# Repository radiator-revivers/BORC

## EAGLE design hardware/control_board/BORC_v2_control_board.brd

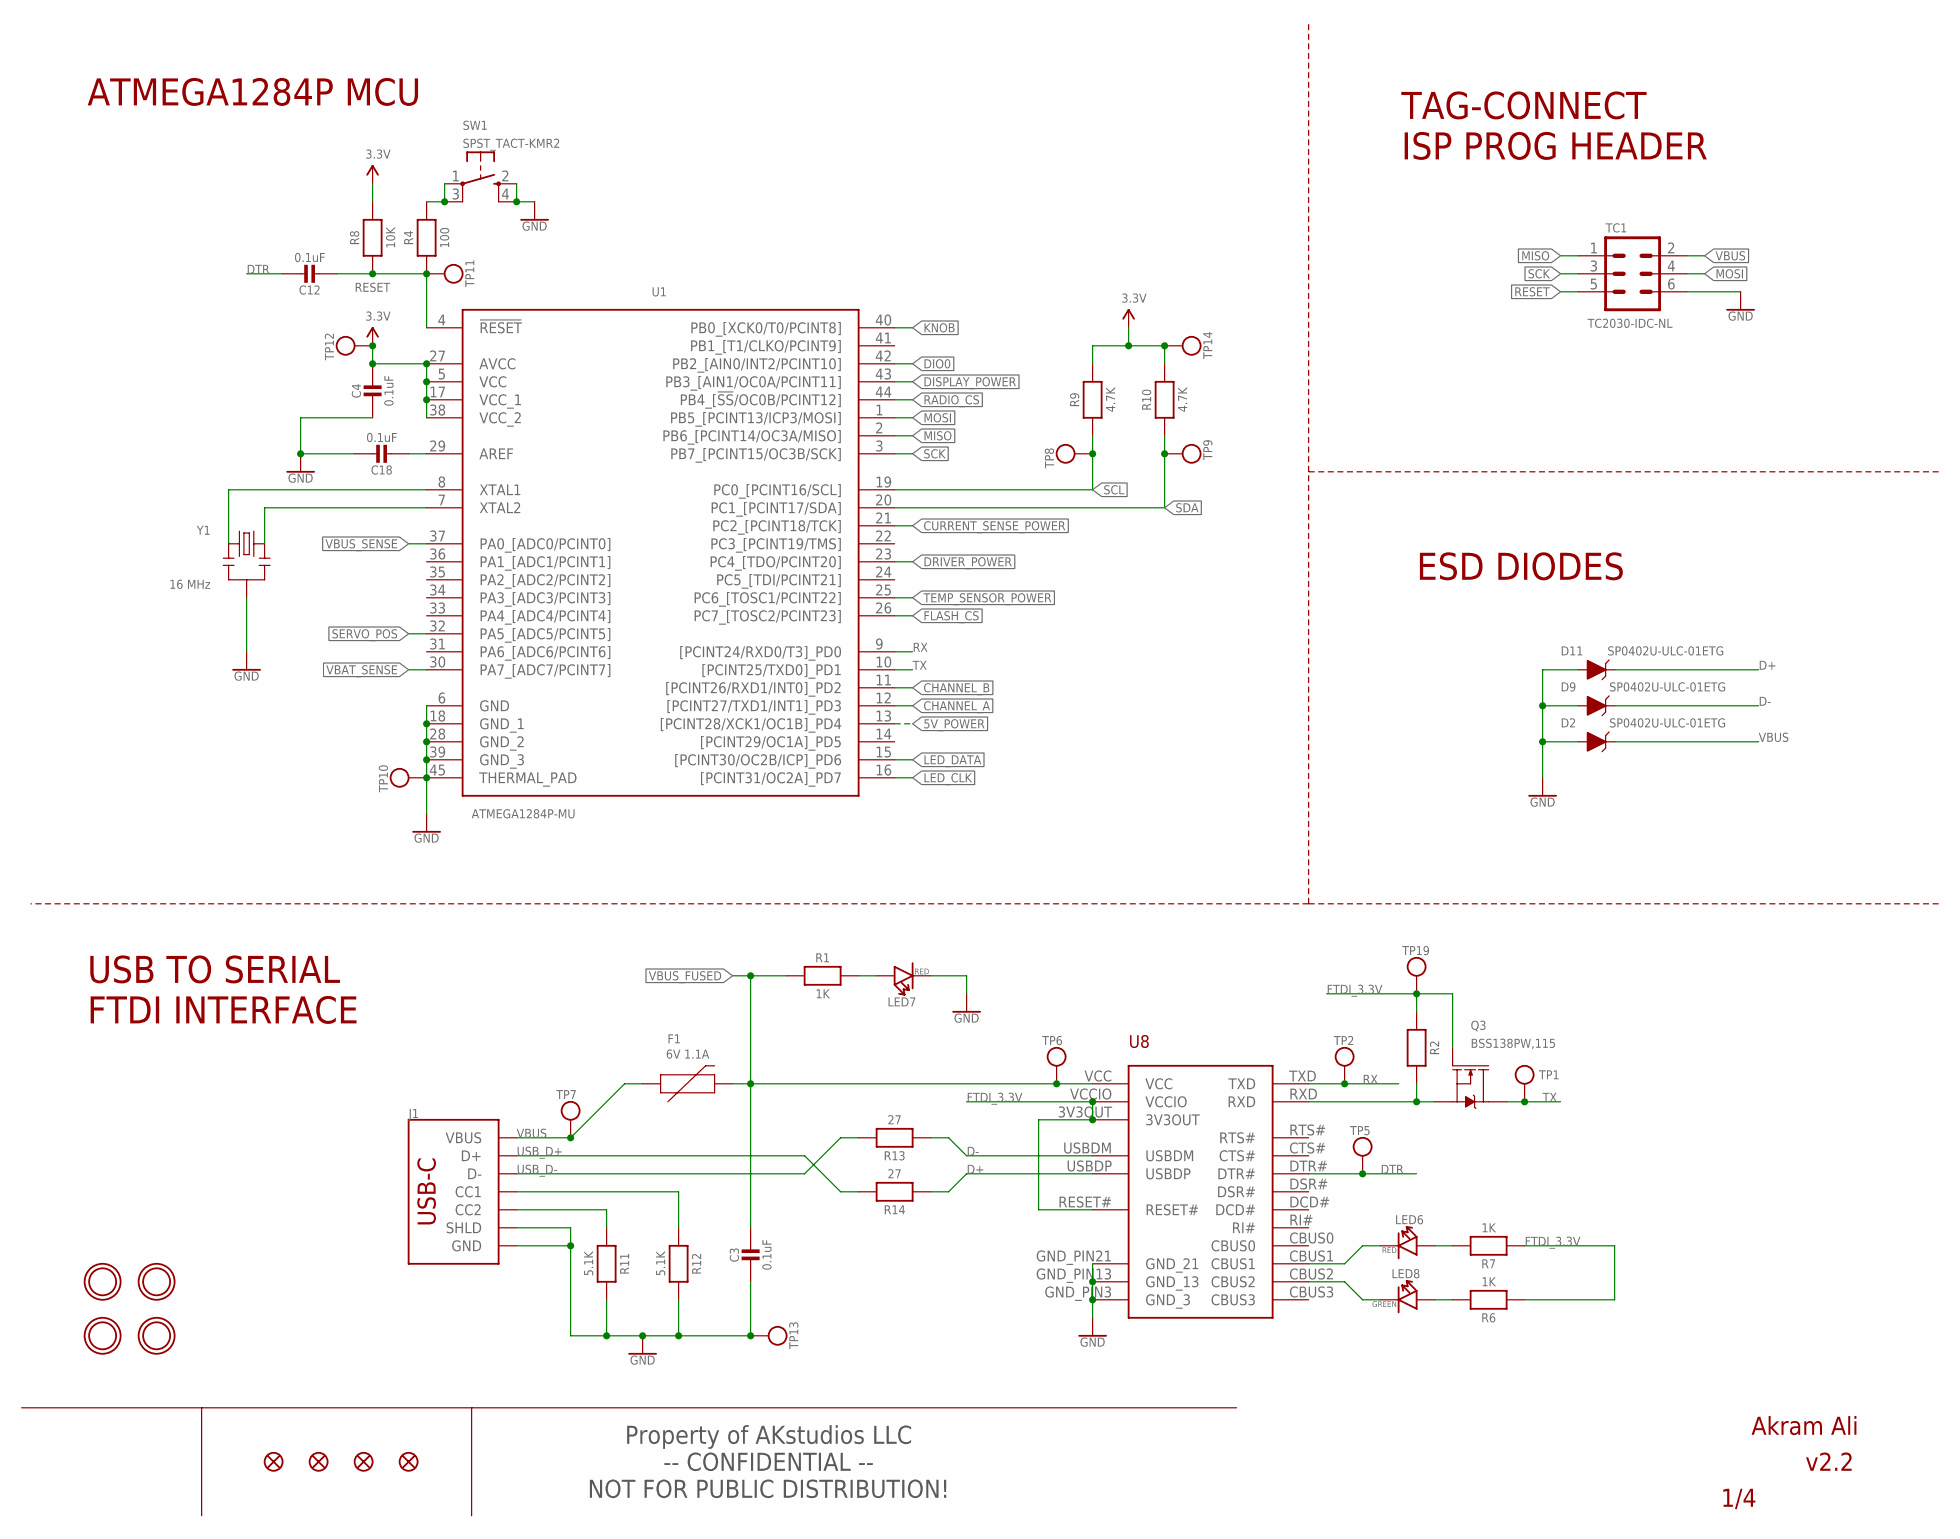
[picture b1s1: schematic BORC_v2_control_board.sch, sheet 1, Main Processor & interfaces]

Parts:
C3, C4, C12, C18: 0.1uF; MICROBUILDER__0402MP; MPN GRM155R71H104KE14D
D2, D9, D11: SP0402U-ULC-01ETG; 0402; MPN SP0402U-ULC-01ETG
F1: 6V 1.1A; 0805; MPN MF-PSML110/6-2
FID1, FID2, FID3, FID4: FIDUCIAL""; FIDUCIAL_1MM
J1: USB Female Type C Connector; USB-C-16P-2LAYER-PADS; MPN USB4105-GF-A
LED6, LED7: RED; LED-0402; MPN IN-S42ATR
LED8: GREEN; LED-0402; MPN IN-S42ATG
Q3: BSS138PW,115; SOT323; MPN BSS138PW,115
R1, R6, R7: 1K; MICROBUILDER__0402MP; MPN RC0402FR-071KL
R2, R8: 10K; MICROBUILDER__0402MP; MPN RC0402FR-7W10KL
R4: 100; MICROBUILDER__0402MP; MPN RC0402FR-07100RL
R9, R10: 4.7K; MICROBUILDER__0402MP; MPN RC0402FR-074K7L
R11, R12: 5.1K; MICROBUILDER__0402MP; MPN RC0402FR-135K1L
R13, R14: 27; MICROBUILDER__0402MP; MPN RC0402FR-0727RL
SW1: SPST_TACT-KMR2; KMR2; MPN KMR221GLFS
TC1: TC2030-IDC-NL
TP1: TX; MICROBUILDER_TESTPOINT_ROUND_1MM
TP2, TP5, TP6, TP7, TP8, TP9, TP10, TP11, TP12, TP13, TP14, TP19: RX; MICROBUILDER_TESTPOINT_ROUND_1MM
U1: ATMEGA1284P-MU; QFN50P700X700X100-45N; MPN ATMEGA1284P-MU
U8: FT231XQ-R; FTDI_FT231XQ-R_PACKAGE
U$8, U$9, U$10, U$11: MICROBUILDER_MOUNTINGHOLE2.5_THICK; MICROBUILDER_MOUNTINGHOLE_2.5_PLATED_THICK
Y1: 16 MHz; RESONATOR-SMD; MPN CSTNE16M0V530000R0

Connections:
5V_POWER: U1.13 ([PCINT28/XCK1/OC1B]_PD4); also elsewhere on the board
CHANNEL_A: U1.12 ([PCINT27/TXD1/INT1]_PD3); also elsewhere on the board
CHANNEL_B: U1.11 ([PCINT26/RXD1/INT0]_PD2); also elsewhere on the board
CURRENT_SENSE_POWER: U1.21 (PC2_[PCINT18/TCK]); also elsewhere on the board
D+: D11.C, R14.1, U8.USBDP
D-: D9.C, R13.1, U8.USBDM
DIO0: U1.42 (PB2_[AIN0/INT2/PCINT10]); also elsewhere on the board
DISPLAY_POWER: U1.43 (PB3_[AIN1/OC0A/PCINT11]); also elsewhere on the board
DRIVER_POWER: U1.23 (PC4_[TDO/PCINT20]); also elsewhere on the board
DTR: C12.1, TP5.P$1, U8.DTR#
FLASH_CS: U1.26 (PC7_[TOSC2/PCINT23]); also elsewhere on the board
FTDI_3.3V: Q3.1 (G), R2.1, R6.1, R7.1, TP19.P$1, U8.3V3OUT, U8.RESET#, U8.VCCIO
GND: C3.2, C4.2, C18.1, D2.A, D9.A, D11.A, J1.GND, J1.GND2 (GND), J1.SHLD1 (SHLD), J1.SHLD2 (SHLD), J1.SHLD3 (SHLD), J1.SHLD4 (SHLD), LED7.-, R11.2, R12.2, SW1.2 (S), SW1.4 (S1), TC1.6, TP10.P$1, TP13.P$1, U1.6 (GND), U1.18 (GND_1), U1.28 (GND_2), U1.39 (GND_3), U1.45 (THERMAL_PAD), U8.GND_PIN3 (GND_3), U8.GND_PIN13 (GND_13), U8.GND_PIN21 (GND_21), Y1.2; also elsewhere on the board
KNOB: U1.40 (PB0_[XCK0/T0/PCINT8]); also elsewhere on the board
LED_CLK: U1.16 ([PCINT31/OC2A]_PD7); also elsewhere on the board
LED_DATA: U1.15 ([PCINT30/OC2B/ICP]_PD6); also elsewhere on the board
MISO: TC1.1, U1.2 (PB6_[PCINT14/OC3A/MISO]); also elsewhere on the board
MOSI: TC1.4, U1.1 (PB5_[PCINT13/ICP3/MOSI]); also elsewhere on the board
unnamed: U1.8 (XTAL1), Y1.1
unnamed: LED7.+, R1.2
unnamed: U1.7 (XTAL2), Y1.3
unnamed: J1.B5 (CC2), R11.1
unnamed: J1.A5 (CC1), R12.1
unnamed: LED8.+, R6.2
unnamed: LED6.-, U8.CBUS1
unnamed: C18.2, U1.29 (AREF)
unnamed: LED8.-, U8.CBUS2
unnamed: R4.2, SW1.1, SW1.3 (P1)
unnamed: Q3.2 (S), R2.2, U8.RXD
unnamed: LED6.+, R7.2
RADIO_CS: U1.44 (PB4_[!SS!/OC0B/PCINT12]); also elsewhere on the board
RESET: C12.2, R4.1, R8.1, TC1.5, TP11.P$1, U1.4 (!RESET)
RX: TP2.P$1, U1.9 ([PCINT24/RXD0/T3]_PD0), U8.TXD
SCK: TC1.3, U1.3 (PB7_[PCINT15/OC3B/SCK]); also elsewhere on the board
SCL: R9.1, TP8.P$1, U1.19 (PC0_[PCINT16/SCL]); also elsewhere on the board
SDA: R10.1, TP9.P$1, U1.20 (PC1_[PCINT17/SDA]); also elsewhere on the board
SERVO_POS: U1.32 (PA5_[ADC5/PCINT5]); also elsewhere on the board
TEMP_SENSOR_POWER: U1.25 (PC6_[TOSC1/PCINT22]); also elsewhere on the board
TX: Q3.3 (D), TP1.P$1, U1.10 ([PCINT25/TXD0]_PD1)
USB_D+: J1.A6 (D+), J1.B6 (D+), R14.2
USB_D-: J1.A7 (D-), J1.B7 (D-), R13.2
VBAT_SENSE: U1.30 (PA7_[ADC7/PCINT7]); also elsewhere on the board
VBUS: D2.C, F1.1, J1.VBUS1 (VBUS), J1.VBUS2 (VBUS), TC1.2, TP7.P$1; also elsewhere on the board
VBUS_FUSED: C3.1, F1.2, R1.1, TP6.P$1, U8.VCC; also elsewhere on the board
VBUS_SENSE: U1.37 (PA0_[ADC0/PCINT0]); also elsewhere on the board
VCC: C4.1, R8.2, R9.2, R10.2, TP12.P$1, TP14.P$1, U1.5 (VCC), U1.17 (VCC_1), U1.27 (AVCC), U1.38 (VCC_2); also elsewhere on the board

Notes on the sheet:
-- CONFIDENTIAL -- NOT FOR PUBLIC DISTRIBUTION!
Property of AKstudios LLC
v2.2
Akram Ali
ATMEGA1284P MCU
TAG-CONNECT ISP PROG HEADER
USB TO SERIAL FTDI INTERFACE
ESD DIODES

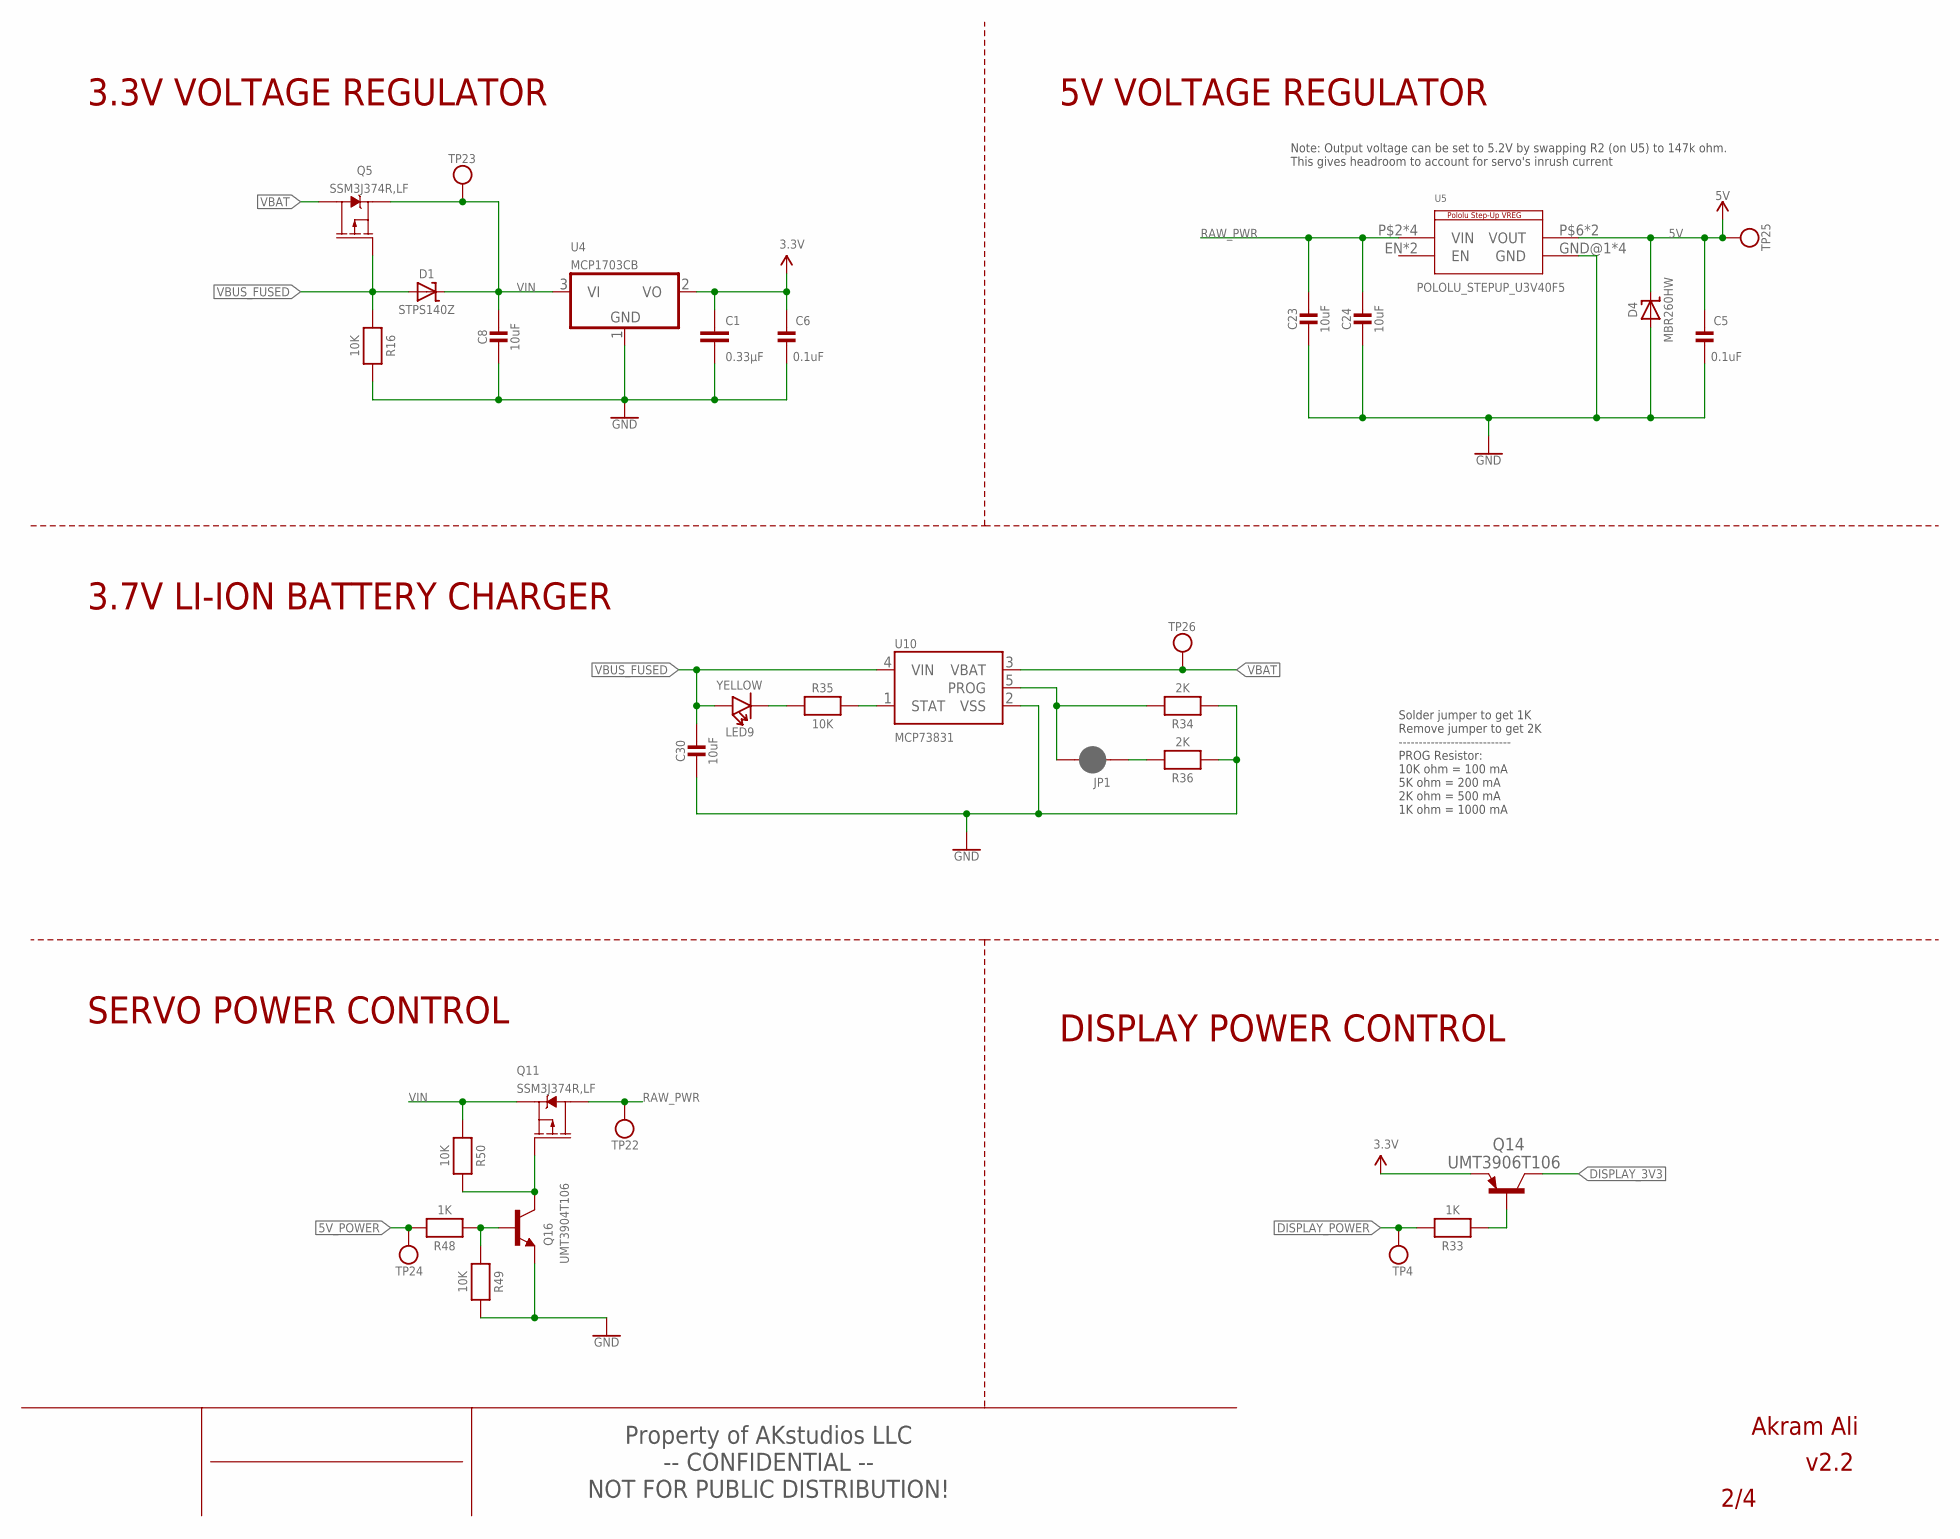
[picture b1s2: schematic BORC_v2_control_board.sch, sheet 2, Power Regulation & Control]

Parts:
C1: 0.33µF; 0805; MPN GRM219R71H334KA88D
C5, C6: 0.1uF; MICROBUILDER__0402MP; MPN GRM155R71H104KE14D
C8, C23, C24: 10uF; MICROBUILDER__0402MP; MPN GRM155R71H104KE14D
C30: 10uF; MICROBUILDER__0402MP; MPN GRM155R61A106ME11D
D1: STPS140Z; SOD-123; MPN STPS140Z
D4: MBR260HW; SOD-123; MPN MBR260HW
JP1: JUMPER-SMT_2_NC_PASTE_SILK; SMT-JUMPER_2_NC_PASTE_SILK
LED9: YELLOW; LED-0402; MPN IN-S42ATY
Q5, Q11: SSM3J374R,LF; SOT23-3; MPN SSM3J374R,LF
Q14: UMT3906T106; SOT65P210X100-3N-PNP; MPN UMT3906T106
Q16: UMT3904T106; SOT65P210X100-3N; MPN UMT3904T106
R16, R35, R49, R50: 10K; MICROBUILDER__0402MP; MPN RC0402FR-7W10KL
R33, R48: 1K; MICROBUILDER__0402MP; MPN RC0402FR-071KL
R34, R36: 2K; MICROBUILDER__0402MP; MPN RC0402FR-072KL
TP4, TP23, TP25, TP26: RX; MICROBUILDER_TESTPOINT_ROUND_1MM
TP22: RAW_PWR; MICROBUILDER_TESTPOINT_ROUND_1MM
TP24: 5V_POWER; MICROBUILDER_TESTPOINT_ROUND_1MM
U4: MCP1703CB; SOT23; MPN MCP1703T-3302E/CB
U5: POLOLU_STEPUP_U3V40F5; POLOLU_STEPUP_U3V40X; MPN U3V40F5
U10: MCP73831; SOT23-5; MPN MCP73831T-2ACI/OT

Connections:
5V: C5.1, D4.C, TP25.P$1, U5.P$6 (VOUT), U5.VOUT; also elsewhere on the board
5V_POWER: R48.2, TP24.P$1; also elsewhere on the board
DISPLAY_3V3: Q14.3 (C); also elsewhere on the board
DISPLAY_POWER: R33.2, TP4.P$1; also elsewhere on the board
GND: C1.2, C5.2, C6.2, C8.2, C23.2, C24.2, C30.2, D4.A, Q16.2 (E), R16.2, R34.1, R36.1, R49.2, U4.1 (GND), U5.GND@1 (GND), U5.GND@2 (GND), U5.P$4 (GND), U5.P$5 (GND), U10.2 (VSS); also elsewhere on the board
unnamed: R35.2, U10.1 (STAT)
unnamed: LED9.-, R35.1
unnamed: Q14.2 (B), R33.1
unnamed: JP1.2, R34.2, U10.5 (PROG)
unnamed: JP1.1, R36.2
unnamed: Q11.1 (G1), Q16.3 (C), R50.2
unnamed: Q16.1 (B), R48.1, R49.1
RAW_PWR: C23.1, C24.1, Q11.3 (D1), TP22.P$1, U5.P$2 (VIN), U5.P$3 (VIN), U5.VIN@1 (VIN), U5.VIN@2 (VIN)
VBAT: Q5.3 (D1), TP26.P$1, U10.3 (VBAT); also elsewhere on the board
VBUS_FUSED: C30.1, D1.A, LED9.+, Q5.1 (G1), R16.1, U10.4 (VIN); also elsewhere on the board
VCC: C1.1, C6.1, Q14.1 (E), U4.2 (VO); also elsewhere on the board
VIN: C8.1, D1.C, Q5.2 (S1), Q11.2 (S1), R50.1, TP23.P$1, U4.3 (VI)

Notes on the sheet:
-- CONFIDENTIAL -- NOT FOR PUBLIC DISTRIBUTION!
Property of AKstudios LLC
v2.2
Akram Ali
3.3V VOLTAGE REGULATOR
5V VOLTAGE REGULATOR
3.7V LI-ION BATTERY CHARGER
Note: Output voltage can be set to 5.2V by swapping R2 (on U5) to 147k ohm. This gives headroom to account for servo's inrush current
SERVO POWER CONTROL
DISPLAY POWER CONTROL
Solder jumper to get 1K Remove jumper to get 2K ---------------------------- PROG Resistor: 10K ohm = 100 mA 5K ohm = 200 mA 2K ohm = 500 mA 1K ohm = 1000 mA

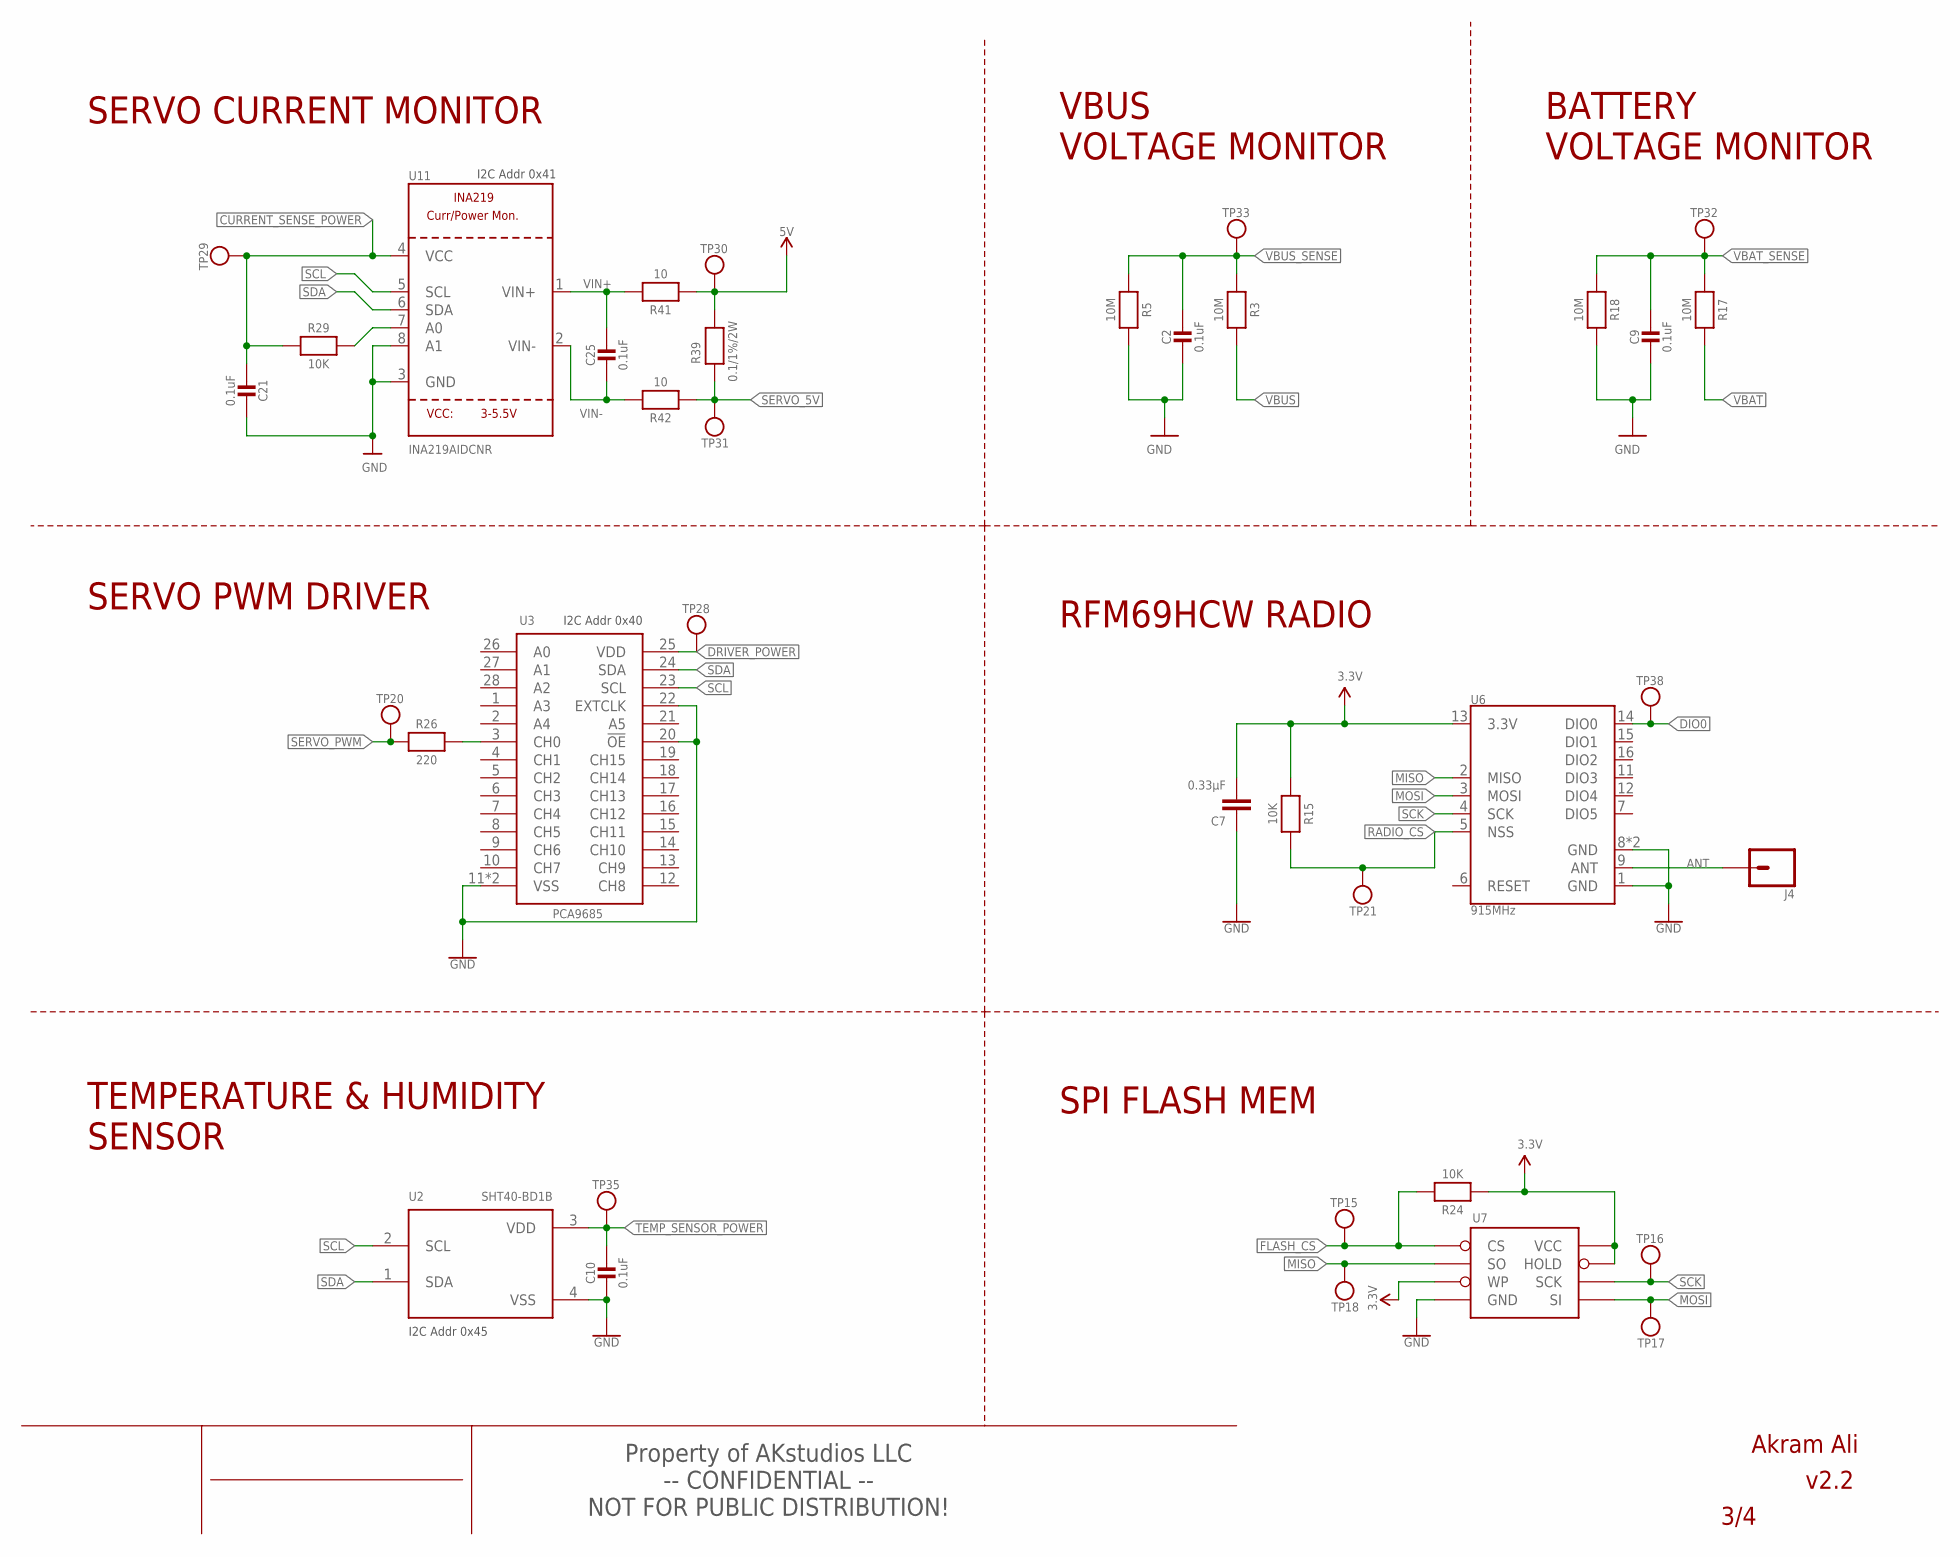
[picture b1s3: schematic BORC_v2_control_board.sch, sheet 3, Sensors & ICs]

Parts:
C2, C9, C10, C21, C25: 0.1uF; MICROBUILDER__0402MP; MPN GRM155R71H104KE14D
C7: 0.33µF; 0805; MPN GRM219R71H334KA88D
J4: CONN_01; 1X01
R3, R5, R17, R18: 10M; MICROBUILDER__0402MP; MPN RC0402FR-0710ML
R15, R24, R29: 10K; MICROBUILDER__0402MP; MPN RC0402FR-7W10KL
R26: 220; MICROBUILDER__0402MP; MPN RC0402FR-13220RL
R39: 0.1/1%/2W; 2512; MPN RCWE2512R100FKEA
R41, R42: 10; MICROBUILDER__0402MP; MPN RC0402FR-07100RL
TP15, TP16, TP17, TP18, TP20, TP21, TP28, TP29, TP30, TP31, TP32, TP33, TP35, TP38: RX; MICROBUILDER_TESTPOINT_ROUND_1MM
U2: SHT40-BD1B; SHT4X; MPN SHT40-BD1B-R3
U3: PCA9685; HVQFN28_SOT788-1; MPN PCA9685BS,118
U6: 915MHz; RFM69HCW-XXXS2
U7: AT25F512BJEDEC_3.9MM; SO08; MPN W25X40CLSNIG
U11: INA219AIDCNR; SOT23-8; MPN INA219AIDCNR

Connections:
5V: R39.2, R41.1, TP30.P$1; also elsewhere on the board
ANT: J4.1, U6.9 (ANT)
CURRENT_SENSE_POWER: C21.2, R29.1, TP29.P$1, U11.4 (VCC); also elsewhere on the board
DIO0: TP38.P$1, U6.14 (DIO0); also elsewhere on the board
DRIVER_POWER: TP28.P$1, U3.25 (VDD); also elsewhere on the board
FLASH_CS: R24.2, TP15.P$1, U7.1_CS (CS); also elsewhere on the board
GND: C2.2, C7.1, C9.2, C10.2, C21.1, R5.2, R18.2, U2.4 (VSS), U3.11 (VSS), U3.20 (!OE), U3.22 (EXTCLK), U3.TH (VSS), U6.1 (GND), U6.8 (GND), U6.10 (GND), U7.4_GND (GND), U11.3 (GND), U11.8 (A1); also elsewhere on the board
MISO: TP18.P$1, U6.2 (MISO), U7.2_SO (SO); also elsewhere on the board
MOSI: TP17.P$1, U6.3 (MOSI), U7.5_SI (SI); also elsewhere on the board
unnamed: R26.2, U3.3 (CH0)
unnamed: R29.2, U11.7 (A0)
RADIO_CS: R15.2, TP21.P$1, U6.5 (NSS); also elsewhere on the board
SCK: TP16.P$1, U6.4 (SCK), U7.6_SCK (SCK); also elsewhere on the board
SCL: U2.2 (SCL), U3.23 (SCL), U11.5 (SCL); also elsewhere on the board
SDA: U2.1 (SDA), U3.24 (SDA), U11.6 (SDA); also elsewhere on the board
SERVO_5V: R39.1, R42.1, TP31.P$1; also elsewhere on the board
SERVO_PWM: R26.1, TP20.P$1; also elsewhere on the board
TEMP_SENSOR_POWER: C10.1, TP35.P$1, U2.3 (VDD); also elsewhere on the board
VBAT: R17.2; also elsewhere on the board
VBAT_SENSE: C9.1, R17.1, R18.1, TP32.P$1; also elsewhere on the board
VBUS: R3.2; also elsewhere on the board
VBUS_SENSE: C2.1, R3.1, R5.1, TP33.P$1; also elsewhere on the board
VCC: C7.2, R15.1, R24.1, U6.13 (3.3V), U7.3_WP (WP), U7.7_HOLD (HOLD), U7.8_VCC (VCC); also elsewhere on the board
VIN+: C25.1, R41.2, U11.1 (VIN+)
VIN-: C25.2, R42.2, U11.2 (VIN-)

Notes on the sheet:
-- CONFIDENTIAL -- NOT FOR PUBLIC DISTRIBUTION!
Property of AKstudios LLC
v2.2
Akram Ali
I2C Addr 0x40
TEMPERATURE & HUMIDITY SENSOR
SERVO PWM DRIVER
I2C Addr 0x45
RFM69HCW RADIO
SERVO CURRENT MONITOR
BATTERY VOLTAGE MONITOR
VBUS VOLTAGE MONITOR
I2C Addr 0x41
SPI FLASH MEM

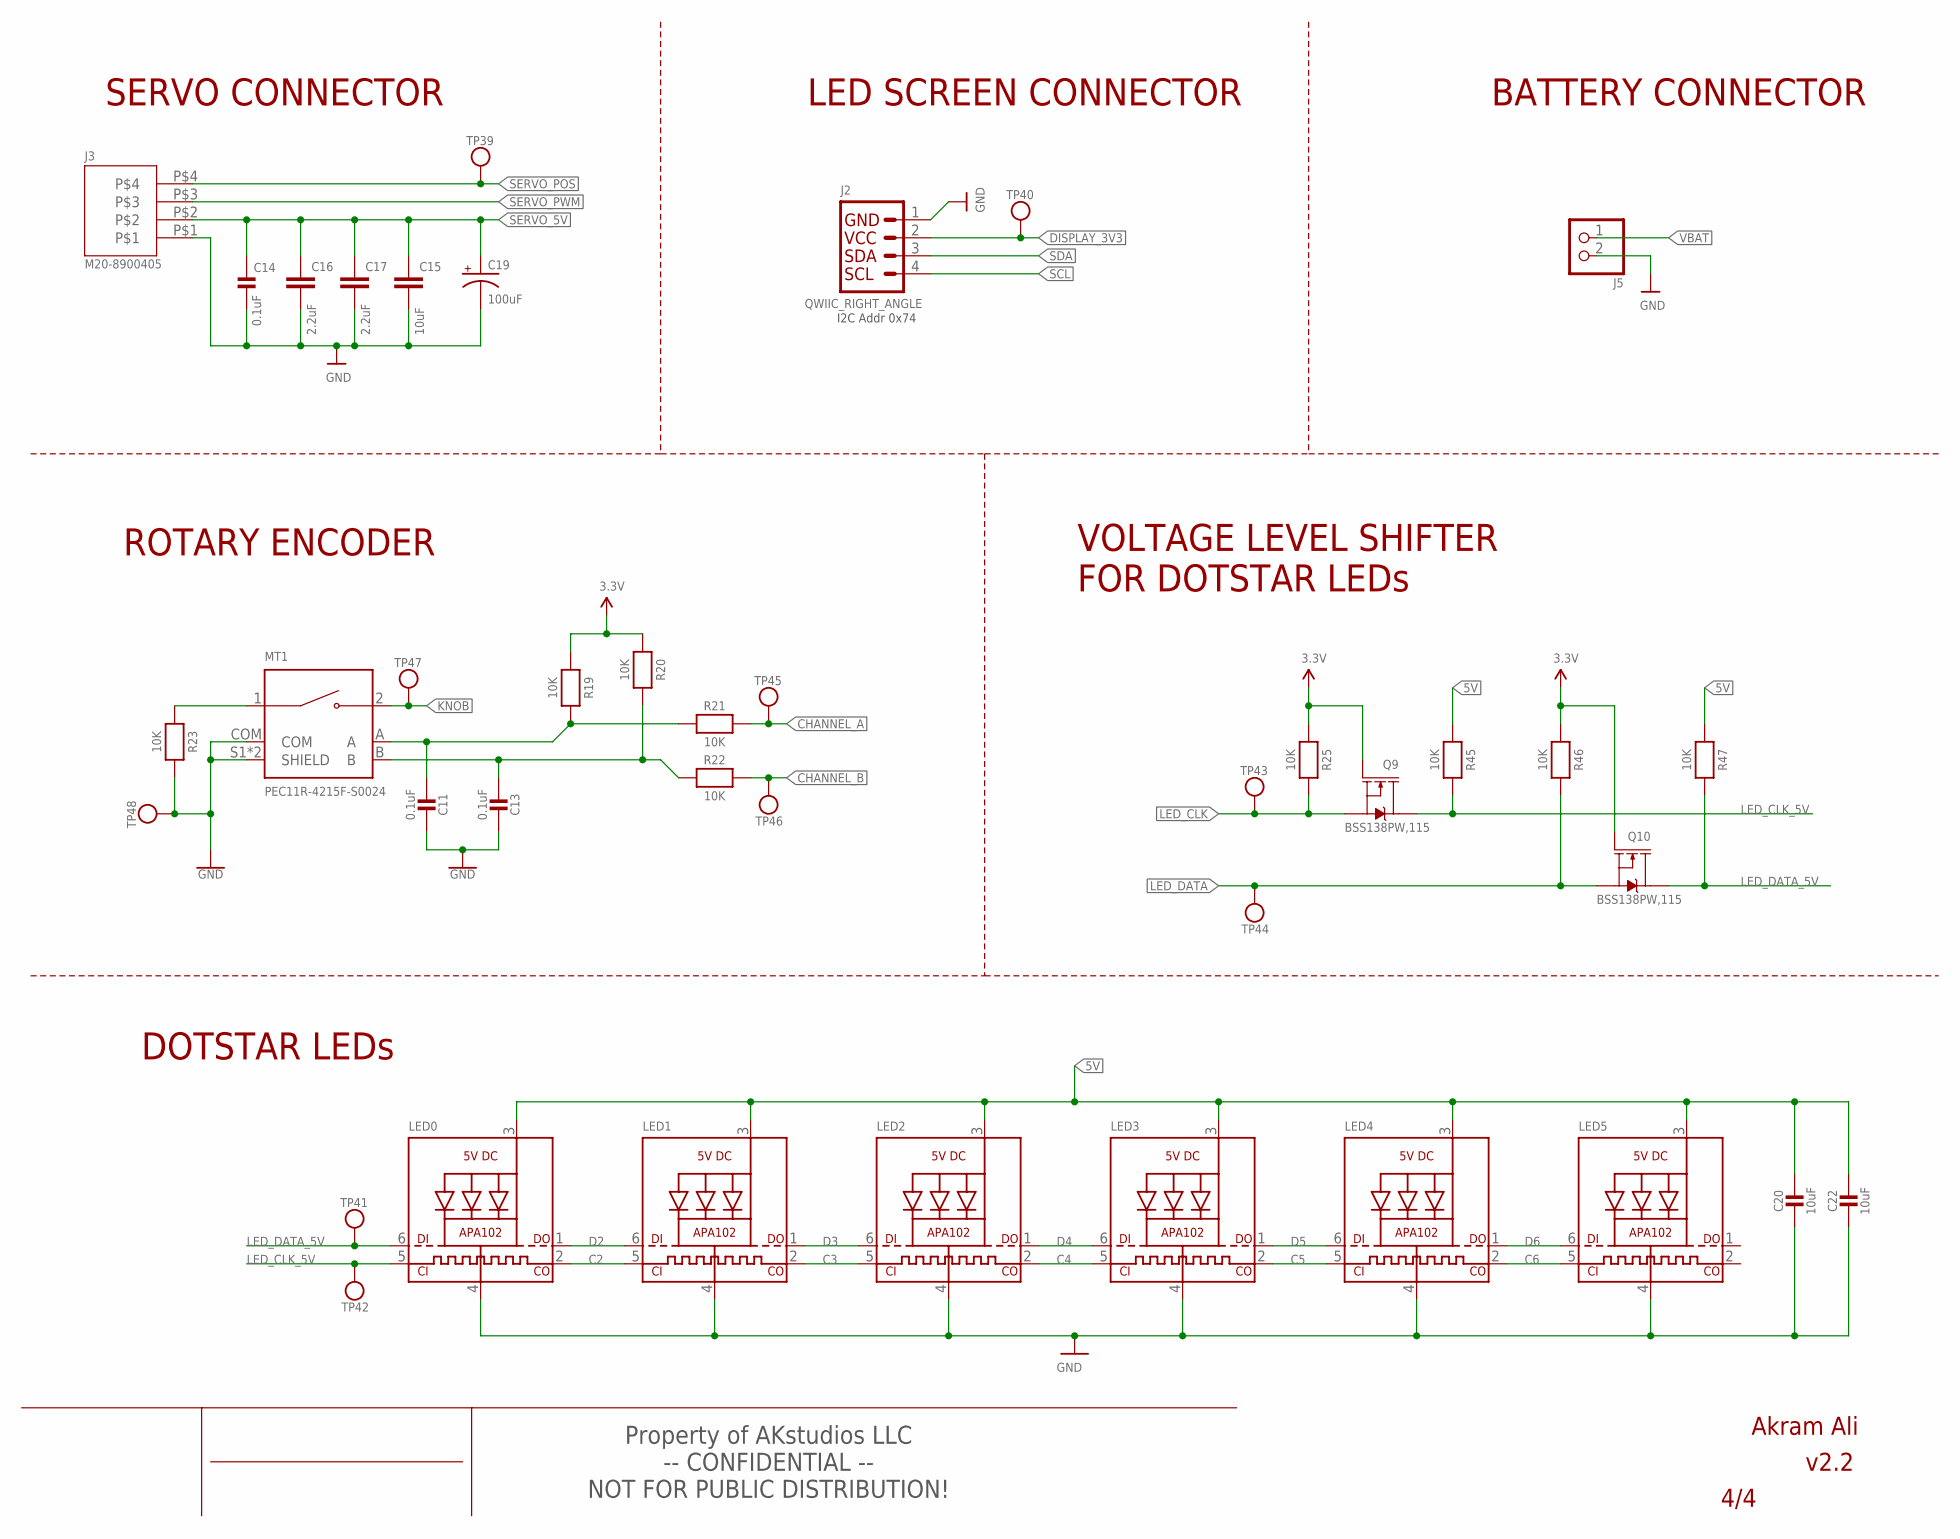
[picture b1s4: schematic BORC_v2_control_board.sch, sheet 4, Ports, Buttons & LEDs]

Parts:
C11, C13: 0.1uF; MICROBUILDER__0402MP; MPN GRM155R71H104KE14D
C14: 0.1uF; 0805-NO; MPN CC0805KRX7R9BB104
C15: 10uF; 0805; MPN GRM21BR61H106KE43L
C16, C17: 2.2uF; 1206
C19: 100uF; PANASONIC_D; MPN A768EB107M1ELAS036
C20, C22: 10uF; MICROBUILDER__0402MP; MPN GRM155R71H104KE14D
J2: QWIIC_RIGHT_ANGLE; JST04_1MM_RA; MPN SM04B-SRSS-TB(LF)(SN)
J3: M20-8900405; MPN M20-8900405
J5: JST_2PIN-THM-RA; JST-PH-2-THM-RA; MPN S2B-PH-K-S
LED0, LED1, LED2, LED3, LED4, LED5: APA102; APA102_2020; MPN APA102-2020
MT1: PEC11R-4215F-S0024; XDCR_PEC11R-4215F-S0024; MPN PEC11R-4215F-S0024
Q9, Q10: BSS138PW,115; SOT323; MPN BSS138PW,115
R19, R20, R21, R22, R23, R25, R45, R46, R47: 10K; MICROBUILDER__0402MP; MPN RC0402FR-7W10KL
TP39, TP40, TP41, TP42, TP43, TP44, TP45, TP46, TP47, TP48: RX; MICROBUILDER_TESTPOINT_ROUND_1MM

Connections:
5V: C20.1, C22.1, LED0.3 (VDD), LED1.3 (VDD), LED2.3 (VDD), LED3.3 (VDD), LED4.3 (VDD), LED5.3 (VDD), R45.1, R47.1; also elsewhere on the board
A: C11.2, MT1.A, R19.2, R21.1
B: C13.2, MT1.B, R20.2, R22.1
C2: LED0.2 (CKO), LED1.5 (CKI)
C3: LED1.2 (CKO), LED2.5 (CKI)
C4: LED2.2 (CKO), LED3.5 (CKI)
C5: LED3.2 (CKO), LED4.5 (CKI)
C6: LED4.2 (CKO), LED5.5 (CKI)
CHANNEL_A: R21.2, TP45.P$1; also elsewhere on the board
CHANNEL_B: R22.2, TP46.P$1; also elsewhere on the board
D2: LED0.1 (DO), LED1.6 (DI)
D3: LED1.1 (DO), LED2.6 (DI)
D4: LED2.1 (DO), LED3.6 (DI)
D5: LED3.1 (DO), LED4.6 (DI)
D6: LED4.1 (DO), LED5.6 (DI)
DISPLAY_3V3: J2.2, TP40.P$1; also elsewhere on the board
GND: C11.1, C13.1, C14.2, C15.2, C16.2, C17.2, C19.-, C20.2, C22.2, J2.1, J3.P$1, J5.2 (1), LED0.4 (GND), LED1.4 (GND), LED2.4 (GND), LED3.4 (GND), LED4.4 (GND), LED5.4 (GND), MT1.COM, MT1.S1 (SHIELD), MT1.S2 (SHIELD), R23.2, TP48.P$1; also elsewhere on the board
KNOB: MT1.2, TP47.P$1; also elsewhere on the board
LED_CLK: Q9.2 (S), R25.2, TP43.P$1; also elsewhere on the board
LED_CLK_5V: LED0.5 (CKI), Q9.3 (D), R45.2, TP42.P$1
LED_DATA: Q10.2 (S), R46.2, TP44.P$1; also elsewhere on the board
LED_DATA_5V: LED0.6 (DI), Q10.3 (D), R47.2, TP41.P$1
unnamed: MT1.1, R23.1
SCL: J2.4; also elsewhere on the board
SDA: J2.3; also elsewhere on the board
SERVO_5V: C14.1, C15.1, C16.1, C17.1, C19.+, J3.P$2; also elsewhere on the board
SERVO_POS: J3.P$4, TP39.P$1; also elsewhere on the board
SERVO_PWM: J3.P$3; also elsewhere on the board
VBAT: J5.1 (2); also elsewhere on the board
VCC: Q9.1 (G), Q10.1 (G), R19.1, R20.1, R25.1, R46.1; also elsewhere on the board

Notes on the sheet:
ROTARY ENCODER
SERVO CONNECTOR
BATTERY CONNECTOR
LED SCREEN CONNECTOR
DOTSTAR LEDs
VOLTAGE LEVEL SHIFTER FOR DOTSTAR LEDs
-- CONFIDENTIAL -- NOT FOR PUBLIC DISTRIBUTION!
Property of AKstudios LLC
v2.2
Akram Ali
I2C Addr 0x74

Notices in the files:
parts and their libraries:
SparkFun-RF: Licensing: Creative Commons ShareAlike 4.0 International - https://creativecommons.org/licenses/by-sa/4.0
